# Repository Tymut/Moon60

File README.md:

# Moon60

---

Moon60 is is a split keyboard with 4x6 column staggered keys, 5 thumb keys and 1 extra key. This was school project related with hobby and evolved into fully functional device.

- Pro micro controller
- MX and Choc compatible, hotswap
- 128x32 OLED
- TRRS connection between sides
- Optional tenting supported by M12 screws
- Reversible PCB

**Firmware:** https://github.com/Nx0dle/qmk_firmware

Moon60 layout was inspired by hands scans from Ergopad (<https://github.com/pashutk/ergopad>) for matrix visualization. Scans were taken from 20 people and merged into subgroups.

Case for this keyboard is designed only for MX style switches (for now)

---

## Hand scans examples

<br>

## CAD render

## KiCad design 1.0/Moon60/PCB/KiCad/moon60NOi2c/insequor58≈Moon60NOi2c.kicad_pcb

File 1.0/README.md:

# Opis projektu klawiatury biometrycznej - Moon60

## Autorzy: Przemek Paciorek, Damian Pryszcz

Wraz z myślą i potrzebami dzisiejszego rynku stworzyliśmy projekt wszechstronnej klawiatury dostosowywanej pod użytkownika.

Dzisiejszy świat opiera się na rozwoju technologii. W wielu jej dziedzinach używane są klawiatury, które na dłuższą metę użytkowania mogą być niebezpieczne. Najpopularniejsze klawiatury, które dominują rynek nie są tworzone z myślą o ergonomii nadgarstków. To właśnie one są najbardziej nadwyrężane w czasie użytkowania klawiatury. Niewłaściwe ułożenie nadgarstków i napięcie jakie wymusza na nas pozycja w której je układamy może wywołać np. zespół cieśni nadgarstka. Również osoby z różnymi dysfunkcjami mogą mieć problemy z użytkowaniem tej jakże potrzebnej części technologii.

W tym celu stworzyliśmy projekt nazwany bazowo **Insequor58**, lecz został on zmodyfikowany i przeniesiony do nazwy **Moon60**. Projekt stworzony został w celu poprawienia ergonomii ułożenia nadgarstków i zmniejszenia ich napięcia, jak i ułatwieniu użytkowania klawiatury przez osoby z dysfunkcjami. Projekt ma za zadanie również zapewnić użytkownikowi możliwie w jak największym stopniu dostosowanie klawiatury pod swoje potrzeby.

### Opcje dostosowania:

- Rozdzielna budowa pozwala na dostosowanie szerokości rozstawu nadgarstków.
- Ułożenie sekcji klawiszy jest zrobione w taki sposób aby zminimalizować ruch nadgarstka.
- Szeroka gama wyboru przełączników pozwala na dostosowanie wysokości jak i odczuć płynących z pisania.
- Podstawka pod nadgarstki wyrównuje napięcie dłoni i podtrzymuje je w jednym miejscu.
- "Tenting", czyli podniesienie poziome klawiatury pozwala na dostosowanie kątu pisania i co za tym idzie ustawienia nadgarstków w bardziej naturalnej pozycji.

### Wykorzystane komponenty:

- Własnoręcznie zaprojektowane PCB
- Diody półprzewodnikowe
- Arduino pro-micro
- Wyświetlacze OLED
- Przełączniki mechaniczne
- Moduły Hot-swap

Dzięki zastosowaniu odpowiedniego firmware klawiatura jest podzielona na dwie części. Wykorzystuje komunikację poprzez przewód TRRS.

"Tenting" i podpórka pod nadgarstki będą modułami magnetycznymi, a do produkcji obudowy i tych komponentów użyliśmy oprogramowania CAD CAM i drukarki 3D.

Mapa i funkcjonalność przycisków została przystosowana do jak najszybszej pracy w wielu dziedzinach. Obecnie do programowania, lecz planujemy rozwój w innych kierunkach.

W przyszłości klawiatura będzie miała możliwość przypisania dowolnych klawiszy w "locie", czyli poprzez wyświetlacz i wgrany na nią firmware, jak i również wyświetlania:

- prędkości pisania
- poziomu ekploatacji komponentów komputera
- efektów graficznych

Planujemy dalszy złożony rozwój projektu i liczymy na liczne rezultaty.

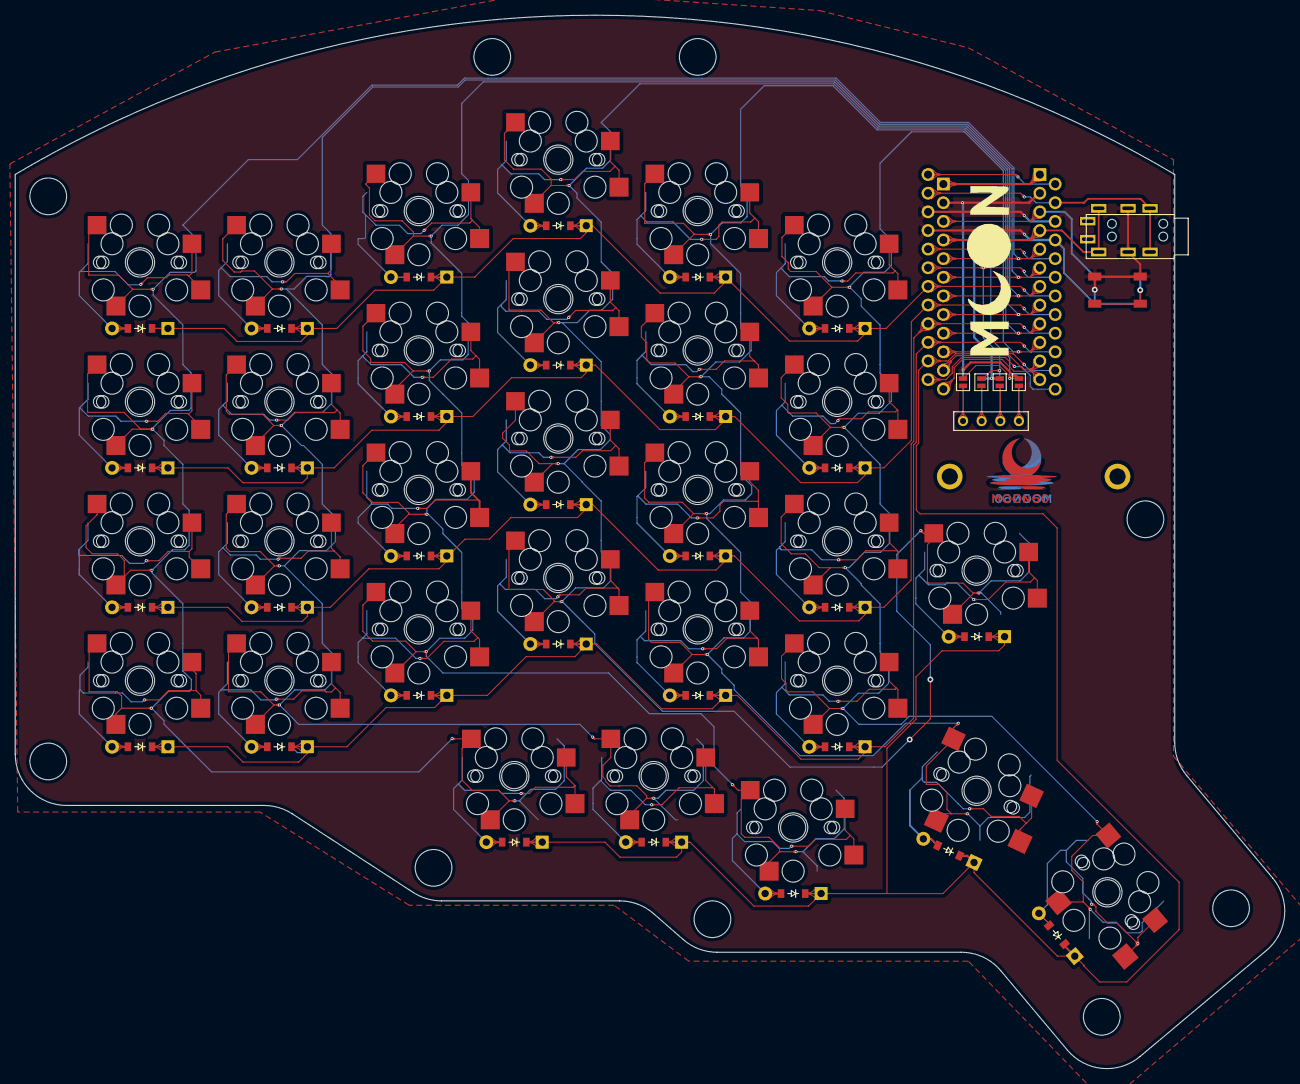
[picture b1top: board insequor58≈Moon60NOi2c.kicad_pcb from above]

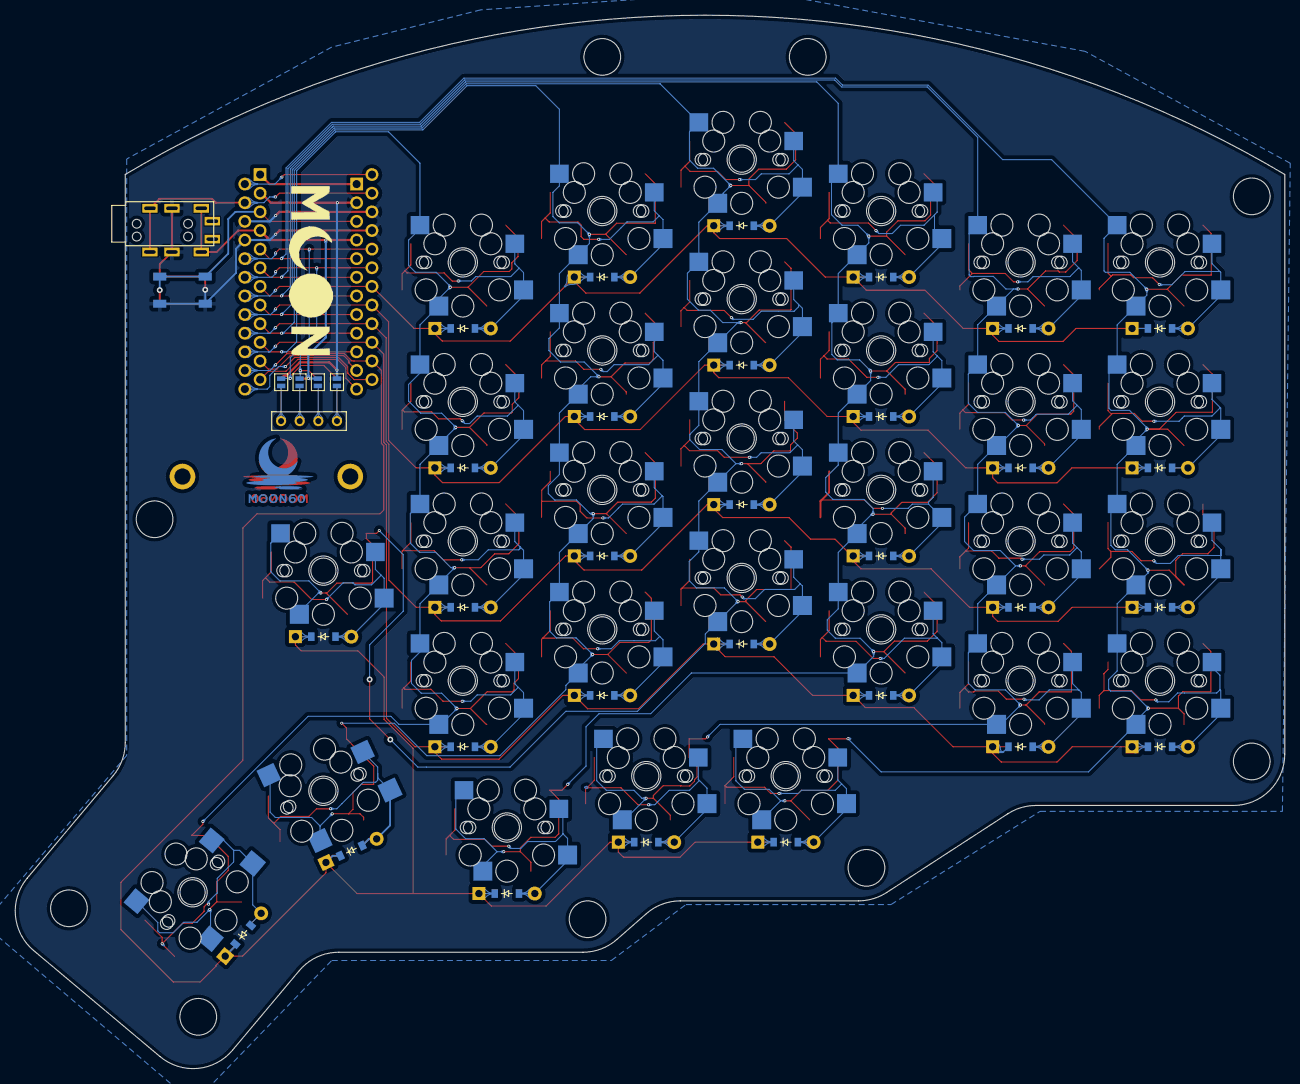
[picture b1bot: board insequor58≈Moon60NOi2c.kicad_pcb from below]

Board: 2 copper layers, 173.0 x 143.5 mm, 104 parts (33 on the bottom side), 22 nets.

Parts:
B1, B1#2: SW_TACT_ALPS_SKQGABE010
D1, D2, D3, D4, D5, D6, D7, D8, D9, D10, D11, D12, D13, D14, D15, D16, D17, D18, D19, D20, D21, D22, D23, D24, D25, D26, D27, D28, D29, D30: ComboDiode
J2: 4PIN; MJ-4PP-9
J3: OLED; OLED_4Pin
JP1, JP2, JP3, JP4, JP5, JP6, JP7, JP8: Jumper
MCU1, MCU2: ProMicro
S1, S3, S5, S7, S9, S11, S13, S15, S17, S19, S21, S23, S25, S27, S29, S31, S33, S35, S37, S39, S41, S43, S45, S47, S49, S51, S53, S55, S57, S59: PG1350
S2, S4, S6, S8, S10, S12, S14, S16, S18, S20, S22, S24, S26, S28, S30, S32, S34, S36, S38, S40, S42, S44, S46, S48, S50, S52, S54, S56, S58, S60: MX

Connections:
GND: B1.1, B1#2.1, J2.2, JP1.2, JP5.2, MCU1.2, MCU1.15, MCU1.16, MCU2.2, MCU2.15, MCU2.16
P0: J2.3, MCU1.14, MCU2.14
P1: MCU1.13, MCU2.13
P2: JP4.2, JP8.2, MCU1.17, MCU2.17
P3: JP3.2, JP7.2, MCU1.18, MCU2.18
P4: D4.1, D4.2, D8.1, D8.2, D12.1, D12.2, D16.1, D16.2, D20.1, D20.2, D24.1, D24.2, MCU1.19, MCU2.19, S7.2, S8.1, S15.2, S16.1, S23.2, S24.1, S31.2, S32.1, S39.2, S40.1, S47.2, S48.1
P5: D3.1, D3.2, D7.1, D7.2, D11.1, D11.2, D15.1, D15.2, D19.1, D19.2, D23.1, D23.2, MCU1.20, MCU2.20, S5.2, S6.1, S13.2, S14.1, S21.2, S22.1, S29.2, S30.1, S37.2, S38.1, S45.2, S46.1
P6: D2.1, D2.2, D6.1, D6.2, D10.1, D10.2, D14.1, D14.2, D18.1, D18.2, D22.1, D22.2, MCU1.21, MCU2.21, S3.2, S4.1, S11.2, S12.1, S19.2, S20.1, S27.2, S28.1, S35.2, S36.1, S43.2, S44.1
P7: D1.1, D1.2, D5.1, D5.2, D9.1, D9.2, D13.1, D13.2, D17.1, D17.2, D21.1, D21.2, MCU1.22, MCU2.22, S1.2, S2.1, S9.2, S10.1, S17.2, S18.1, S25.2, S26.1, S33.2, S34.1, S41.2, S42.1
P8: D25.1, D25.2, D26.1, D26.2, D27.1, D27.2, D28.1, D28.2, D29.1, D29.2, D30.1, D30.2, MCU1.23, MCU2.23, S49.2, S50.1, S51.2, S52.1, S53.2, S54.1, S55.2, S56.1, S57.2, S58.1, S59.2, S60.1
P9: MCU1.24, MCU2.24
P10: MCU1.12, MCU2.12
P14: MCU1.10, MCU2.10, S41.1, S42.2, S43.1, S44.2, S45.1, S46.2, S47.1, S48.2, S59.1, S60.2
P15: MCU1.9, MCU2.9, S33.1, S34.2, S35.1, S36.2, S37.1, S38.2, S39.1, S40.2, S57.1, S58.2
P16: MCU1.11, MCU2.11
P18: MCU1.8, MCU2.8, S25.1, S26.2, S27.1, S28.2, S29.1, S30.2, S31.1, S32.2, S55.1, S56.2
P19: MCU1.7, MCU2.7, S17.1, S18.2, S19.1, S20.2, S21.1, S22.2, S23.1, S24.2, S53.1, S54.2
P20: MCU1.6, MCU2.6, S9.1, S10.2, S11.1, S12.2, S13.1, S14.2, S15.1, S16.2, S51.1, S52.2
P21: MCU1.5, MCU2.5, S1.1, S2.2, S3.1, S4.2, S5.1, S6.2, S7.1, S8.2, S49.1, S50.2
RAW: MCU1.1, MCU2.1
RST: B1.2, B1#2.2, MCU1.3, MCU2.3
VCC: J2.1, JP2.2, JP6.2, MCU1.4, MCU2.4

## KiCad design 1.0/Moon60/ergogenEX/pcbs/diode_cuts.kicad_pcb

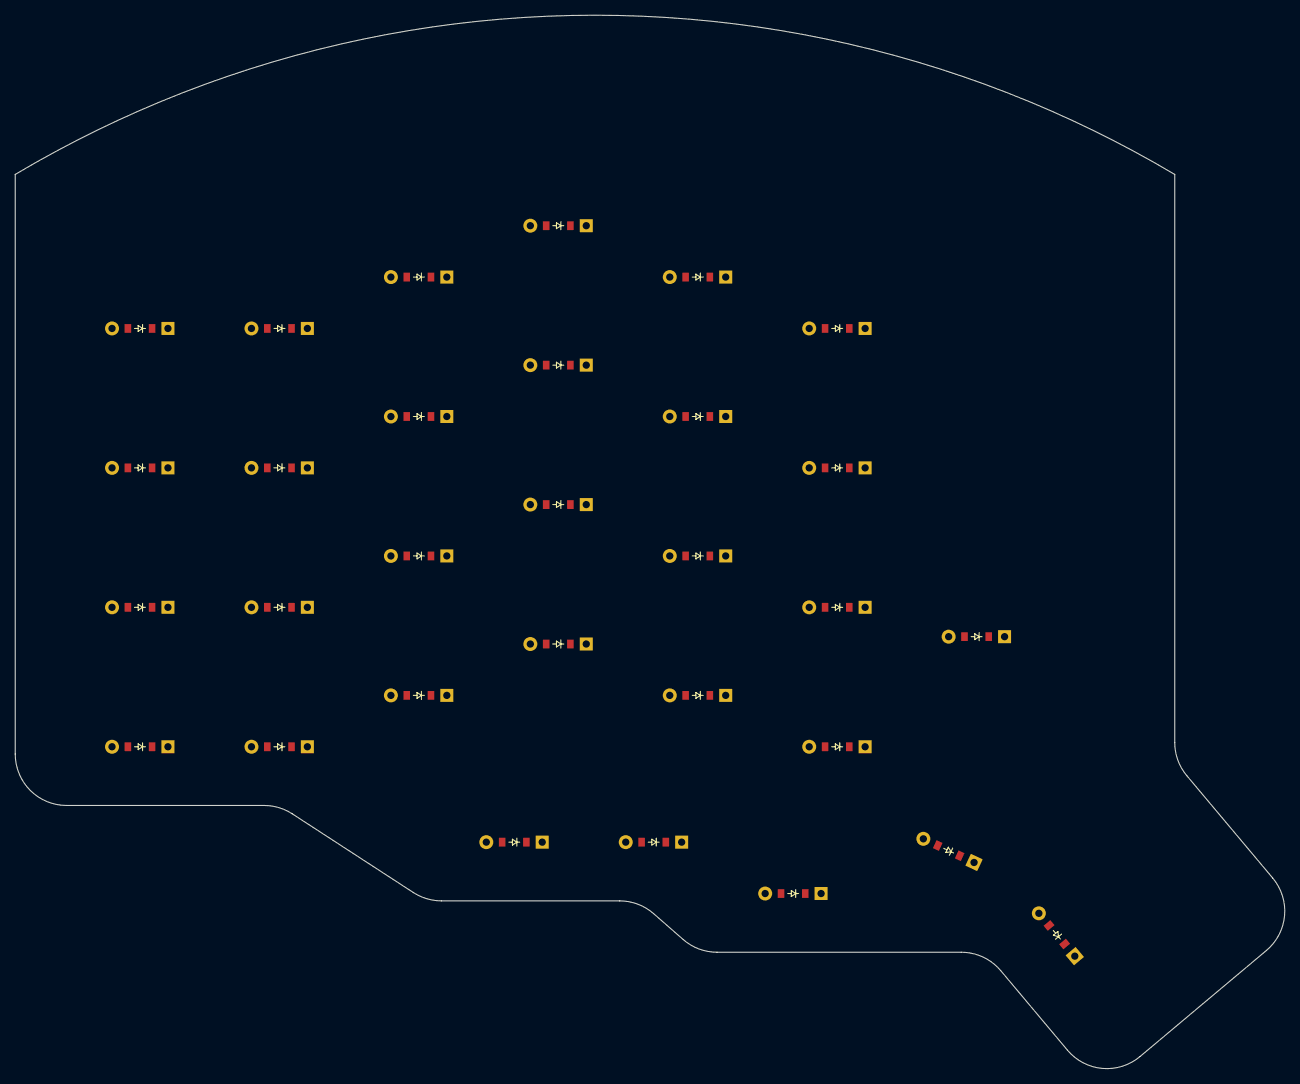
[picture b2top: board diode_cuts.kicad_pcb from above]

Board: 2 copper layers, 173.0 x 143.5 mm, 30 parts (0 on the bottom side), 2 nets, no tracks yet.

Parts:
D1, D2, D3, D4, D5, D6, D7, D8, D9, D10, D11, D12, D13, D14, D15, D16, D17, D18, D19, D20, D21, D22, D23, D24, D25, D26, D27, D28, D29, D30: ComboDiode

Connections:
{{column_net}}: D1.1, D2.1, D3.1, D4.1, D5.1, D6.1, D7.1, D8.1, D9.1, D10.1, D11.1, D12.1, D13.1, D14.1, D15.1, D16.1, D17.1, D18.1, D19.1, D20.1, D21.1, D22.1, D23.1, D24.1, D25.1, D26.1, D27.1, D28.1, D29.1, D30.1
{{row_net}}: D1.2, D2.2, D3.2, D4.2, D5.2, D6.2, D7.2, D8.2, D9.2, D10.2, D11.2, D12.2, D13.2, D14.2, D15.2, D16.2, D17.2, D18.2, D19.2, D20.2, D21.2, D22.2, D23.2, D24.2, D25.2, D26.2, D27.2, D28.2, D29.2, D30.2

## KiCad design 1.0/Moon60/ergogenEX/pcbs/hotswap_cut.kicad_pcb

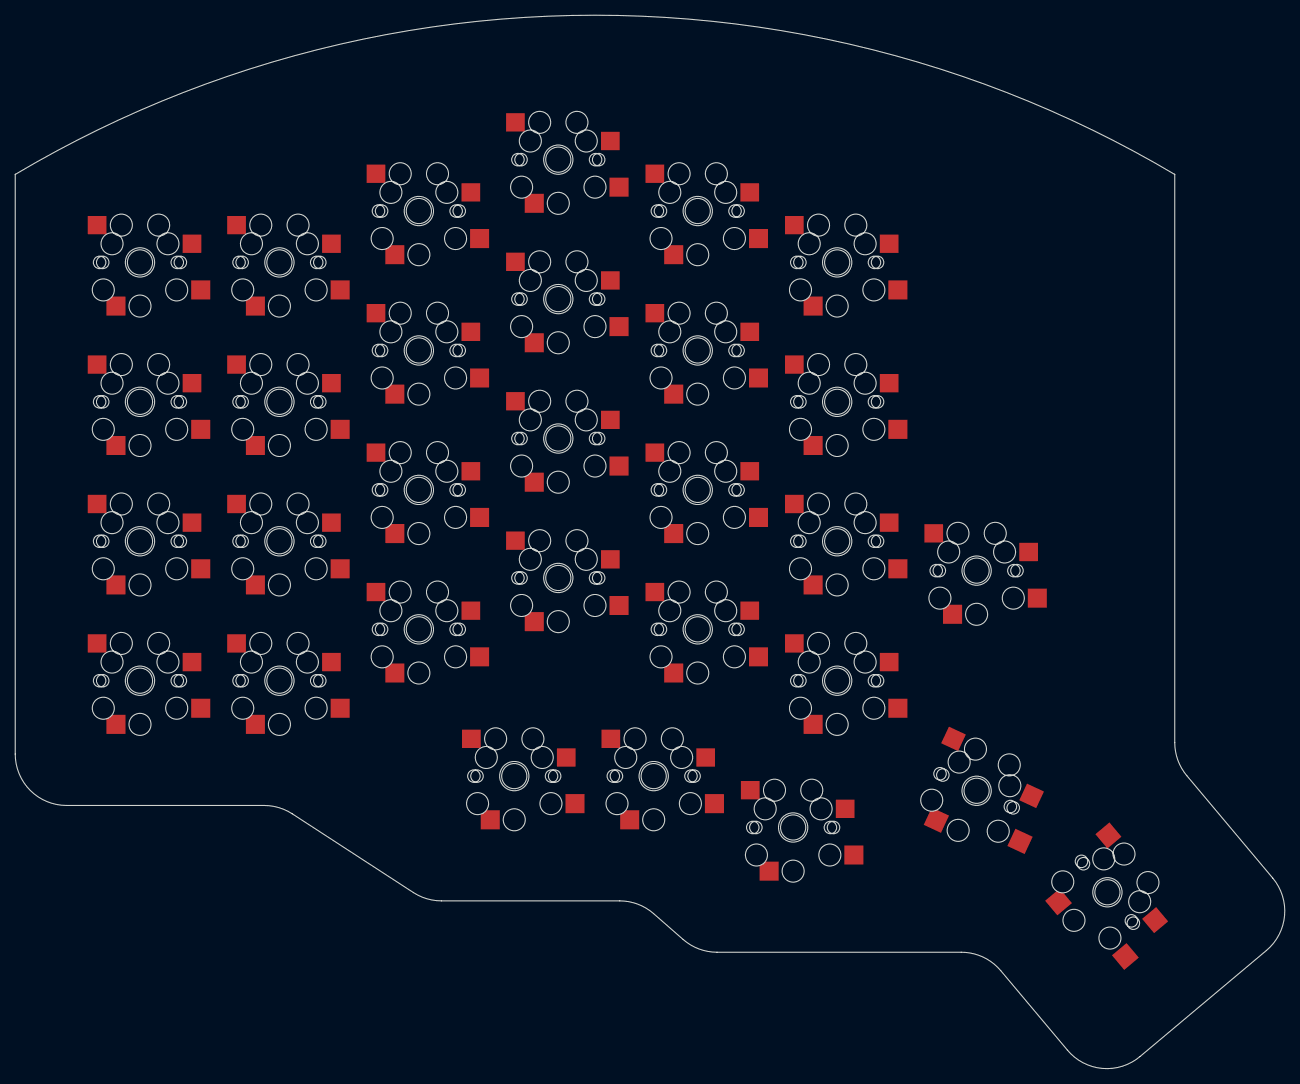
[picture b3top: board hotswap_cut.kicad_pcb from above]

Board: 2 copper layers, 173.0 x 143.5 mm, 60 parts (0 on the bottom side), 2 nets, no tracks yet.

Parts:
S1, S2, S3, S4, S5, S6, S7, S8, S9, S10, S11, S12, S13, S14, S15, S16, S17, S18, S19, S20, S21, S22, S23, S24, S25, S26, S27, S28, S29, S30: PG1350
S31, S32, S33, S34, S35, S36, S37, S38, S39, S40, S41, S42, S43, S44, S45, S46, S47, S48, S49, S50, S51, S52, S53, S54, S55, S56, S57, S58, S59, S60: MX

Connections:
{{column_net}}: S1.2, S2.2, S3.2, S4.2, S5.2, S6.2, S7.2, S8.2, S9.2, S10.2, S11.2, S12.2, S13.2, S14.2, S15.2, S16.2, S17.2, S18.2, S19.2, S20.2, S21.2, S22.2, S23.2, S24.2, S25.2, S26.2, S27.2, S28.2, S29.2, S30.2, S31.2, S32.2, S33.2, S34.2, S35.2, S36.2, S37.2, S38.2, S39.2, S40.2, S41.2, S42.2, S43.2, S44.2, S45.2, S46.2, S47.2, S48.2, S49.2, S50.2, S51.2, S52.2, S53.2, S54.2, S55.2, S56.2, S57.2, S58.2, S59.2, S60.2
{{row_net}}: S1.1, S2.1, S3.1, S4.1, S5.1, S6.1, S7.1, S8.1, S9.1, S10.1, S11.1, S12.1, S13.1, S14.1, S15.1, S16.1, S17.1, S18.1, S19.1, S20.1, S21.1, S22.1, S23.1, S24.1, S25.1, S26.1, S27.1, S28.1, S29.1, S30.1, S31.1, S32.1, S33.1, S34.1, S35.1, S36.1, S37.1, S38.1, S39.1, S40.1, S41.1, S42.1, S43.1, S44.1, S45.1, S46.1, S47.1, S48.1, S49.1, S50.1, S51.1, S52.1, S53.1, S54.1, S55.1, S56.1, S57.1, S58.1, S59.1, S60.1

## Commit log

2022-10-10 Layouts
2022-10-11 Stable 0.1 ver.
2022-10-14 Ver0.2 (Case-rebuild, .dfx-sorted, definition-added)
2022-10-14 file rename
2022-10-14 README.md update
2022-10-15 Ver0.5 (footprints-rebuild, nets-added)
2022-10-15 Rename/README.md update
2022-10-15 v0.6 (positions-fixed)
2022-10-16 v0.6.1 (outlines-scaled_up, plate_fixed)
2022-10-20 v0.7 (mounting_holes-fixed, wireless-BETA)
2022-10-21 v0.7.1 (topMount-BETA)
2022-10-23 v0.9 (topMount, trayMount, positions-fixed)
2022-10-23 v9.1 (promicro_platecut-fixed [optional])
2022-10-23 v9.2 (plateCutOLD-optional)
2022-10-23 v0.9.2 (switch_slots-update)
2022-10-24 v0.9.3
2022-10-24 v0.9.4 (position-update)
2022-10-25 v0.9.5 (sizing-fixing [work in progress])
2022-10-29 v0.9.6 (sizing and positionig [work in progress])
2022-10-29 Insequor58 v1.0 stableAssembly
    Footprints-positionsFixed, added optional switch, mounting-fixed
2022-10-29 Insequor58 v1.0 stableAssembly
2022-10-29 KiCad filesAdded
2022-10-29 v1.0.1 (tracing-fixed)
2022-10-30 v1.0.2 (nets-repair)
2022-11-01 README.me
2022-11-01 README.md updates
2022-11-01 Added firmware files [work in progress]
2022-11-01 .json file added
2022-11-01 KiCad update
2022-11-02 v1.0.3 (nets-workInProgress)
2022-11-02 KiCad filesUpdate
2022-11-02 KiCad files update
2022-11-03 Dodanie schematu Bottom Case w formacie pdf
2022-11-04 Moon60 name update
2022-11-05 Add files via upload
    Dodanie poprawionego schematu obudowy
2022-11-05 Opis projektu.txt added
2022-11-05 Files update
2022-11-05 readme update
2022-11-05 README updates
2022-11-05 unnecessary
2022-11-08 Moved to other repo
2022-11-10 Logo added
2022-11-10 v1.0.5 (Final PCB)
2022-11-10 v1.0.6 (Plate finishing touches)
2022-11-10 Images added
2022-11-10 KiCad moon60 footprints added
2022-11-10 Author and name added
2022-11-27 v1.0.6 (Plate screw holes fixed)
2022-11-27 Plate update
2022-11-27 v1.0.7 (plate.stl adjust)
2022-11-27 v1.0.8 (experimental plate thickness adjust)
2022-11-27 Old files
2022-11-29 Addition of tenting images
2022-11-29 Infographic added
2022-12-03 Posters rebuild
2022-12-08 README
2022-12-09 Prepairing for 2.0
2022-12-11 Spliting project to 1.0 and 2.0
2022-12-11 Cleaning up
2022-12-22 v0.0.1 basic shape
2022-12-22 merged qmk firmware
2022-12-22 merged main qmk
2022-12-22 ergogen exports update
2022-12-22 Example OLED QMK logo
2022-12-22 QMK logo example fixed
2022-12-29 Active layer function
2022-12-29 const layers name fixed
2022-12-31 Added split kb functions definition
2022-12-31 Enabling WPM function
2023-01-02 WPM function ( by copy & paste )
2023-01-02 MOON60 LogoBIG32 image (beta)
2023-01-04 Fast fix layout of code
2023-01-05 Syntax amendments
2023-01-10 1.0 PCB splitted to I2C and non I2C ver (building)
2023-01-11 Moon60Symbols.kicad_sym
2023-01-11 1.0 WRONG PCB setted
2023-01-11 Tenting supports model added
2023-01-11 config.h and keymap in readme update
2023-01-11 Major adjustments to keymap (qmk update)
2023-01-11 product usb info moved
2023-01-11 info.json usb descriptor fix
2023-01-11 3DP arround PCB files added
2023-01-12 1.0 PCB quick fix
2023-01-14 qmk swap hands enable and logo render
2023-01-19 QMK fm moved to main folder
2023-01-23 2.0 starting point
2023-01-25 Prep/edu for ergogen v4.0 update
2023-01-27 merged from 2.0-shelf
2023-01-27 moved to branch
2023-01-27 Successful migrate to v4.0 ergogen
2023-01-27 Nets tracking improved
2023-01-27 top frame and bottom case sketches added ~ metric
2023-01-27 added 0.5mm offsets to case and frame
2023-01-27 gap fix
2023-01-29 bottom wall thickness decrrease
2023-01-30 TRS connectror routing update
2023-01-30 same
2023-02-04 mcu reversible and plate offset sketch
2023-02-04 footprints minor changes
2023-02-07 added top frame components cut
2023-02-08 hotswapcut added
2023-02-13 PCB manufacturing
2023-02-17 merging from PC
2023-03-02 Major changes for final split PCB
2023-03-03 via implementation
2023-03-04 via implementation fix
2023-03-04 re-merging items
2023-03-14 test merge
2023-03-14 small update for oled with LUNA base
2023-03-15 Luna anim delete + media layer try
2023-05-11 kicad layers scan + minor changes to keymap
2023-06-28 luna add
2023-11-23 Create LICENSE
2023-11-23 Update LICENSE
2023-12-11 oled refresh problem fix
2023-12-11 hand swap enable
2024-06-18 repository reorganize - remove old files
2024-06-18 license update
2024-06-18 main README update
2024-06-18 quick README link update
